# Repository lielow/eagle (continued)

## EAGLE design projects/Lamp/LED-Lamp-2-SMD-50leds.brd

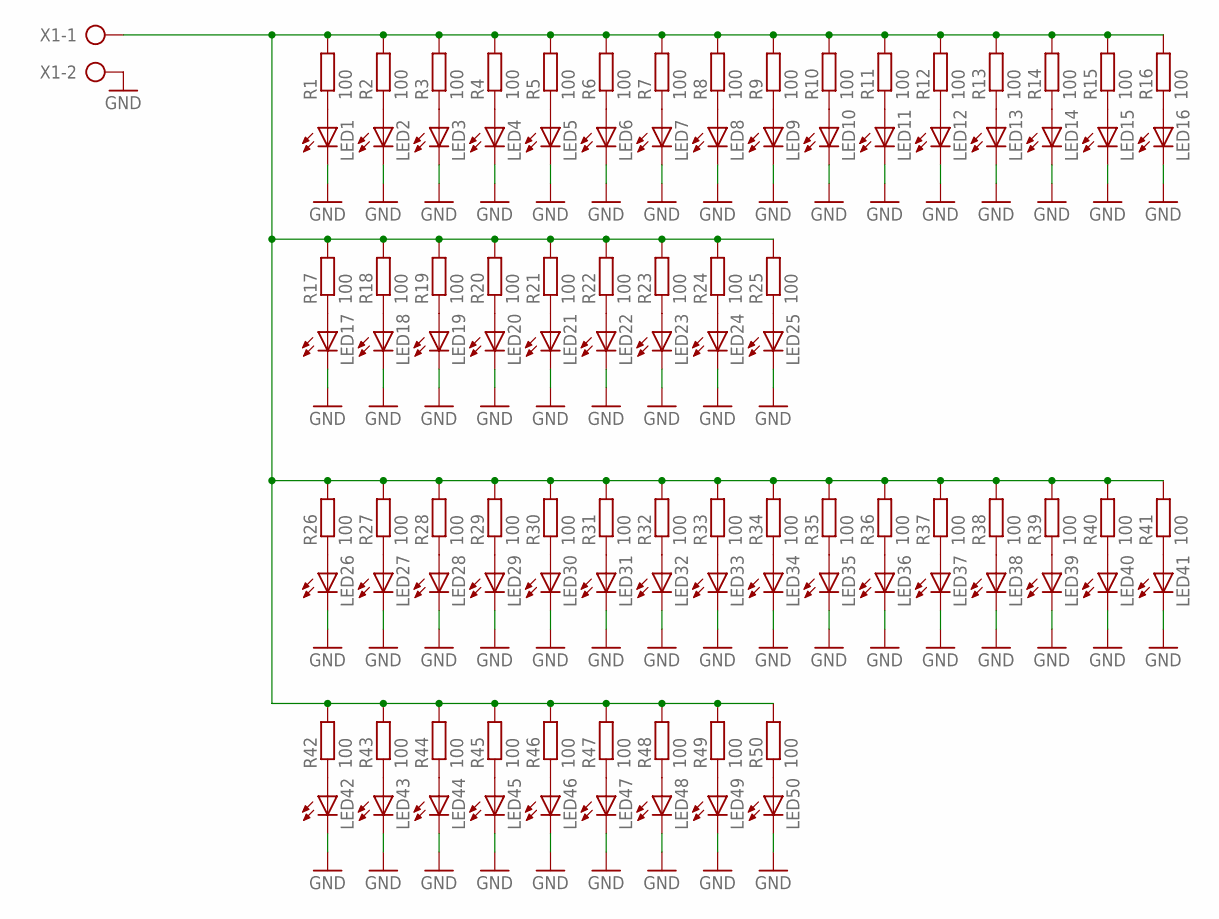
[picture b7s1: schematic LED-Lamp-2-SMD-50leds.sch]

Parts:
LED1, LED2, LED3, LED4, LED5, LED6, LED7, LED8, LED9, LED10, LED11, LED12, LED13, LED14, LED15, LED16, LED17, LED18, LED19, LED20, LED21, LED22, LED23, LED24, LED25, LED26, LED27, LED28, LED29, LED30, LED31, LED32, LED33, LED34, LED35, LED36, LED37, LED38, LED39, LED40, LED41, LED42, LED43, LED44, LED45, LED46, LED47, LED48, LED49, LED50: LEDSML0805; SML0805
R1, R2, R3, R4, R5, R6, R7, R8, R9, R10, R11, R12, R13, R14, R15, R16, R17, R18, R19, R20, R21, R22, R23, R24, R25, R26, R27, R28, R29, R30, R31, R32, R33, R34, R35, R36, R37, R38, R39, R40, R41, R42, R43, R44, R45, R46, R47, R48, R49, R50: 100; M0805
X1: AK300/2

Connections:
GND: LED1.C, LED2.C, LED3.C, LED4.C, LED5.C, LED6.C, LED7.C, LED8.C, LED9.C, LED10.C, LED11.C, LED12.C, LED13.C, LED14.C, LED15.C, LED16.C, LED17.C, LED18.C, LED19.C, LED20.C, LED21.C, LED22.C, LED23.C, LED24.C, LED25.C, LED26.C, LED27.C, LED28.C, LED29.C, LED30.C, LED31.C, LED32.C, LED33.C, LED34.C, LED35.C, LED36.C, LED37.C, LED38.C, LED39.C, LED40.C, LED41.C, LED42.C, LED43.C, LED44.C, LED45.C, LED46.C, LED47.C, LED48.C, LED49.C, LED50.C, X1.2
unnamed: LED1.A, R1.1
unnamed: LED26.A, R26.1
unnamed: LED27.A, R27.1
unnamed: LED2.A, R2.1
unnamed: R1.2, R2.2, R3.2, R4.2, R5.2, R6.2, R7.2, R8.2, R9.2, R10.2, R11.2, R12.2, R13.2, R14.2, R15.2, R16.2, R17.2, R18.2, R19.2, R20.2, R21.2, R22.2, R23.2, R24.2, R25.2, R26.2, R27.2, R28.2, R29.2, R30.2, R31.2, R32.2, R33.2, R34.2, R35.2, R36.2, R37.2, R38.2, R39.2, R40.2, R41.2, R42.2, R43.2, R44.2, R45.2, R46.2, R47.2, R48.2, R49.2, R50.2, X1.1
unnamed: LED3.A, R3.1
unnamed: LED28.A, R28.1
unnamed: LED4.A, R4.1
unnamed: LED29.A, R29.1
unnamed: LED5.A, R5.1
unnamed: LED31.A, R31.1
unnamed: LED6.A, R6.1
unnamed: LED30.A, R30.1
unnamed: LED7.A, R7.1
unnamed: LED32.A, R32.1
unnamed: LED8.A, R8.1
unnamed: LED33.A, R33.1
unnamed: LED9.A, R9.1
unnamed: LED34.A, R34.1
unnamed: LED10.A, R10.1
unnamed: LED35.A, R35.1
unnamed: LED11.A, R11.1
unnamed: LED36.A, R36.1
unnamed: LED12.A, R12.1
unnamed: LED37.A, R37.1
unnamed: LED13.A, R13.1
unnamed: LED38.A, R38.1
unnamed: LED14.A, R14.1
unnamed: LED39.A, R39.1
unnamed: LED15.A, R15.1
unnamed: LED41.A, R41.1
unnamed: LED16.A, R16.1
unnamed: LED40.A, R40.1
unnamed: LED17.A, R17.1
unnamed: LED42.A, R42.1
unnamed: LED18.A, R18.1
unnamed: LED43.A, R43.1
unnamed: LED19.A, R19.1
unnamed: LED44.A, R44.1
unnamed: LED20.A, R20.1
unnamed: LED45.A, R45.1
unnamed: LED21.A, R21.1
unnamed: LED46.A, R46.1
unnamed: LED22.A, R22.1
unnamed: LED47.A, R47.1
unnamed: LED23.A, R23.1
unnamed: LED48.A, R48.1
unnamed: LED24.A, R24.1
unnamed: LED49.A, R49.1
unnamed: LED25.A, R25.1
unnamed: LED50.A, R50.1

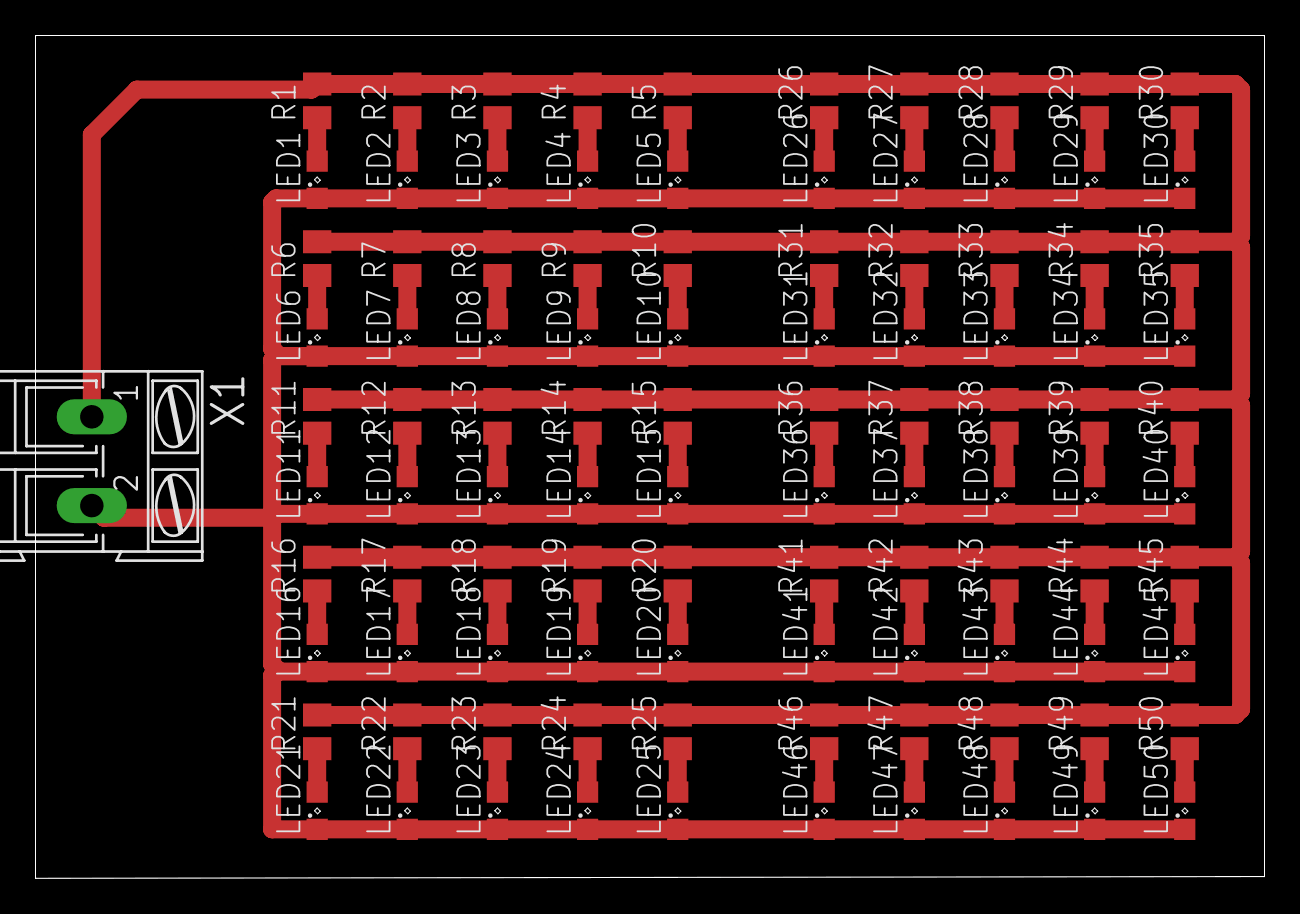
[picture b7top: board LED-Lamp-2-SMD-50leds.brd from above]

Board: 2 copper layers, 69.3 x 47.5 mm, 101 parts (0 on the bottom side), 52 nets.

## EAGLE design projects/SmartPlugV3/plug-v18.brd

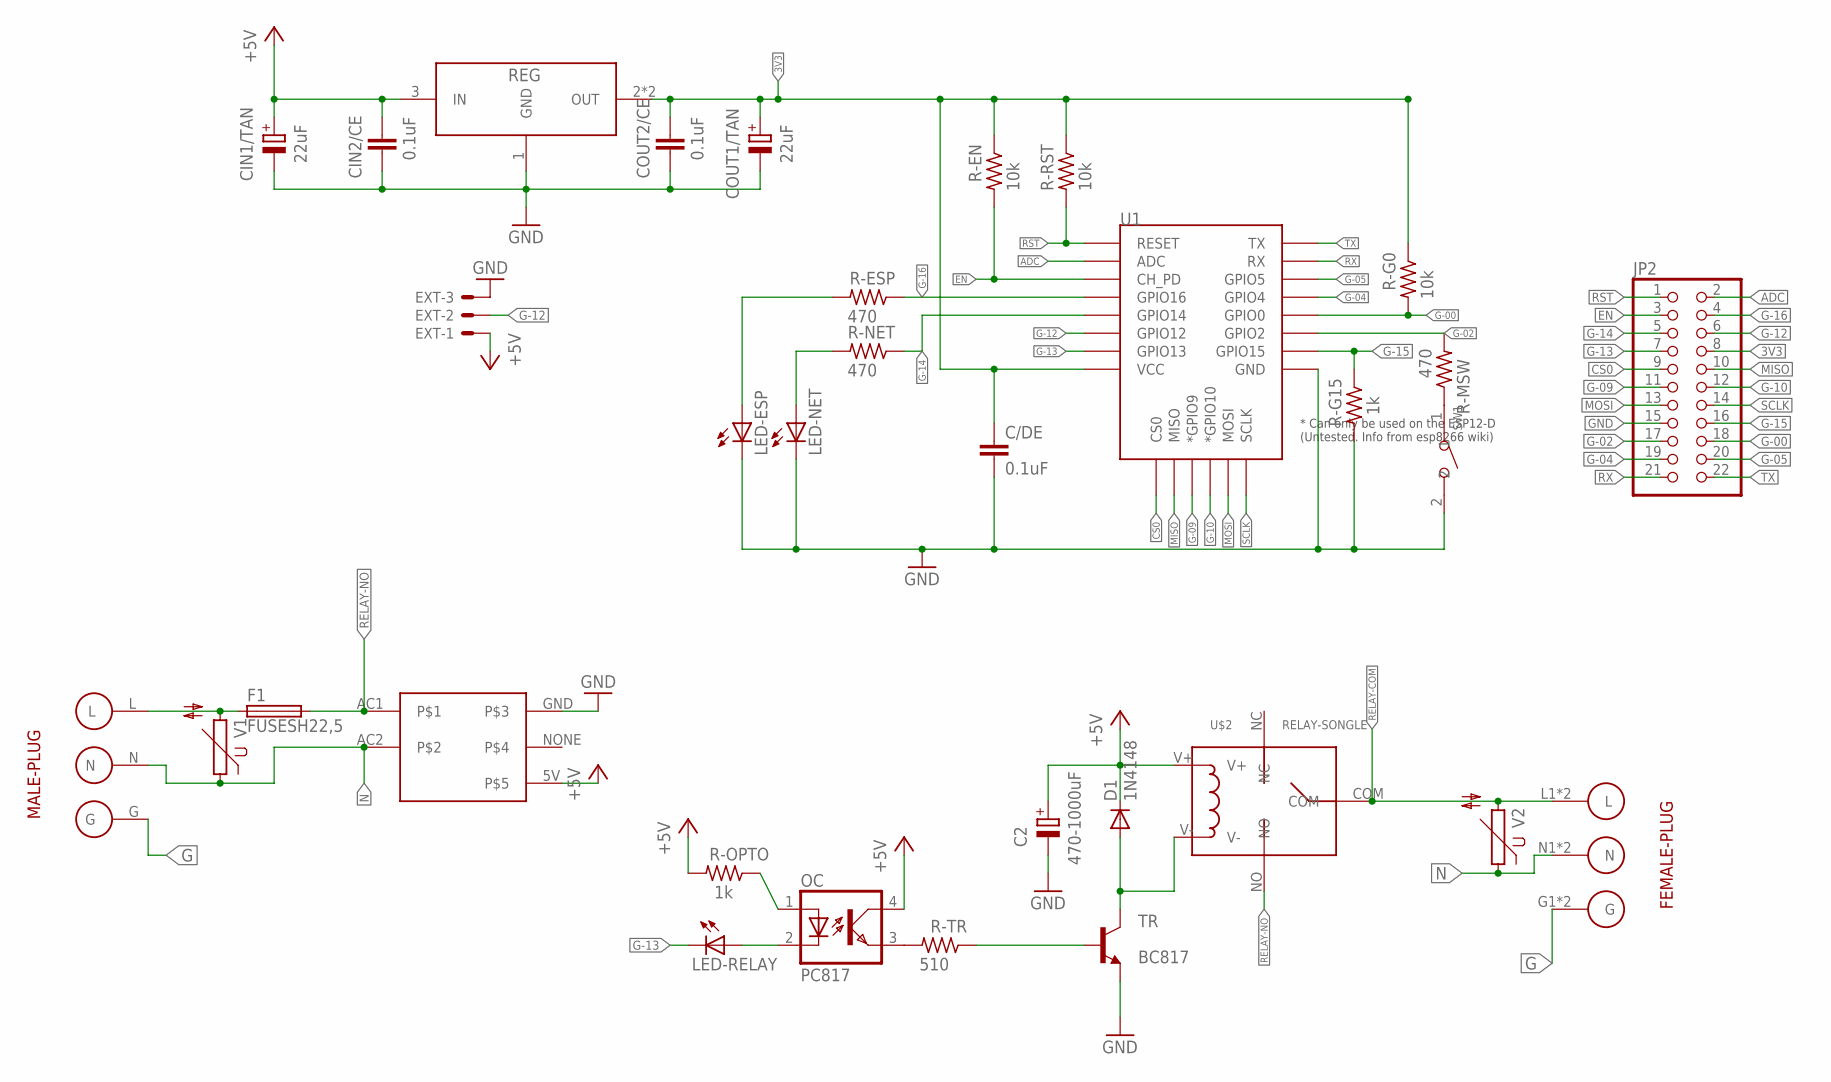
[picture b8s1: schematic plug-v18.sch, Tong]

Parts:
C2: 470-1000uF; E3,5-8
C/DE: 0.1uF; C0805
CIN1/TAN: 22uF; B/3528-21R
CIN2/CE: 0.1uF; C0805K
COUT1/TAN: 22uF; B/3528-21R
COUT2/CE: 0.1uF; C0805K
D1: 1N4148; DO35-7
EXT: 53048-03
F1: FUSESH22,5; SH22,5
JP2: PINHD-2X11; 2X11
LED-ESP: LEDCHIPLED_0805; CHIPLED_0805
LED-NET: LEDCHIPLED_0805; CHIPLED_0805
LED-RELAY: LEDCHIPLED_0805; CHIPLED_0805
OC: PC817; DIL04
R-EN: 10k; M0805
R-ESP: 470; M0805
R-G0: 10k; M0805
R-G15: 1k; M0805
R-MSW: 470; M0805
R-NET: 470; M0805
R-OPTO: 1k; M0805
R-RST: 10k; M0805
R-TR: 510; M0805
REG: AMS1117-3.3; SOT-223
SW1: DIP-BUTTON(2P-6.0X3.0X4.3MM)-TS-1101F; SW2-5.0-6.0X3.0X4.3MM
TR: BC817; SOT23-BEC
U1: ESP12ESMD; ESP12E-SMD
U$2: RELAY-SONGLE
U$3: MALE-PLUG
U$4: POWERSUPPLY-5V-700MA
U$5: FEMALE-PLUG
V1, V2: S14K11

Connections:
3V3: C/DE.1, COUT1/TAN.+, COUT2/CE.1, JP2.8, R-EN.1, R-G0.1, R-RST.1, REG.2 (OUT), REG.4 (OUT), U1.VCC
+5V: C2.+, CIN1/TAN.+, CIN2/CE.1, D1.C, EXT.1, OC.4 (COL), R-OPTO.2, REG.3 (IN), U$2.V+, U$4.5V
ADC: JP2.2, U1.ADC
CS0: JP2.9, U1.CS0
EN: JP2.3, R-EN.2, U1.CH_PD
G: U$3.G, U$5.G1 (G), U$5.G2 (G)
G-00: JP2.18, R-G0.2, U1.GPIO0
G-02: JP2.17, R-MSW.2, U1.GPIO2
G-04: JP2.19, U1.GPIO4
G-05: JP2.20, U1.GPIO5
G-09: JP2.11, U1.GPIO9 (*GPIO9)
G-10: JP2.12, U1.GPIO10 (*GPIO10)
G-12: EXT.2, JP2.6, U1.GPIO12
G-13: JP2.7, LED-RELAY.C, U1.GPIO13
G-14: JP2.5, R-NET.1, U1.GPIO14
G-15: JP2.16, R-G15.1, U1.GPIO15
G-16: JP2.4, R-ESP.1, U1.GPIO16
GND: C2.-, C/DE.2, CIN1/TAN.-, CIN2/CE.2, COUT1/TAN.-, COUT2/CE.2, EXT.3, JP2.15, LED-ESP.C, LED-NET.C, R-G15.2, REG.1 (GND), SW1.2, TR.E, U1.GND, U$4.GND
LINE: F1.1, U$3.L, V1.2
MISO: JP2.10, U1.MISO
MOSI: JP2.13, U1.MOSI
N: U$3.N, U$4.AC2, U$5.N1 (N), U$5.N2 (N), V1.1, V2.1
unnamed: OC.3 (EMIT), R-TR.2
unnamed: R-TR.1, TR.B
unnamed: LED-ESP.A, R-ESP.2
unnamed: OC.1 (A), R-OPTO.1
unnamed: LED-NET.A, R-NET.2
unnamed: D1.A, TR.C, U$2.V-
unnamed: LED-RELAY.A, OC.2 (C)
unnamed: R-MSW.1, SW1.1
RELAY-COM: U$2.COM, U$5.L1 (L), U$5.L2 (L), V2.2
RELAY-NO: F1.2, U$2.NO, U$4.AC1
RST: JP2.1, R-RST.2, U1.RESET
RX: JP2.21, U1.RXD0 (RX)
SCLK: JP2.14, U1.SCLK
TX: JP2.22, U1.TXD0 (TX)

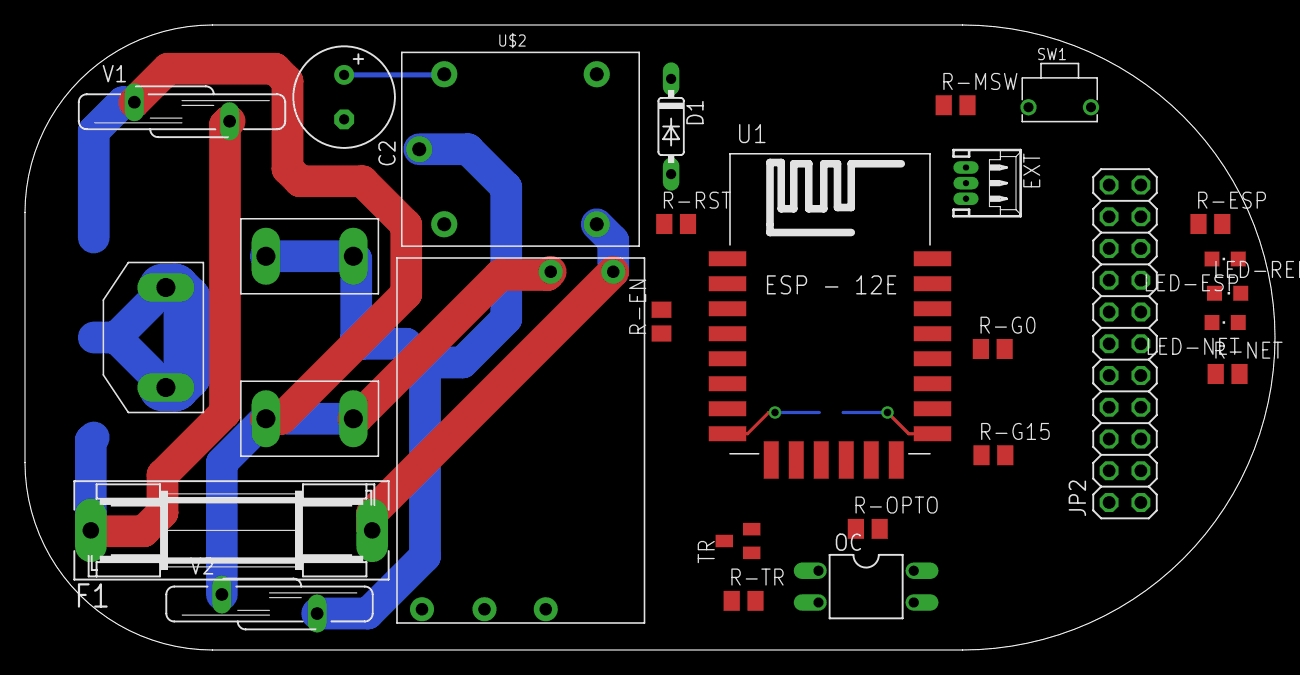
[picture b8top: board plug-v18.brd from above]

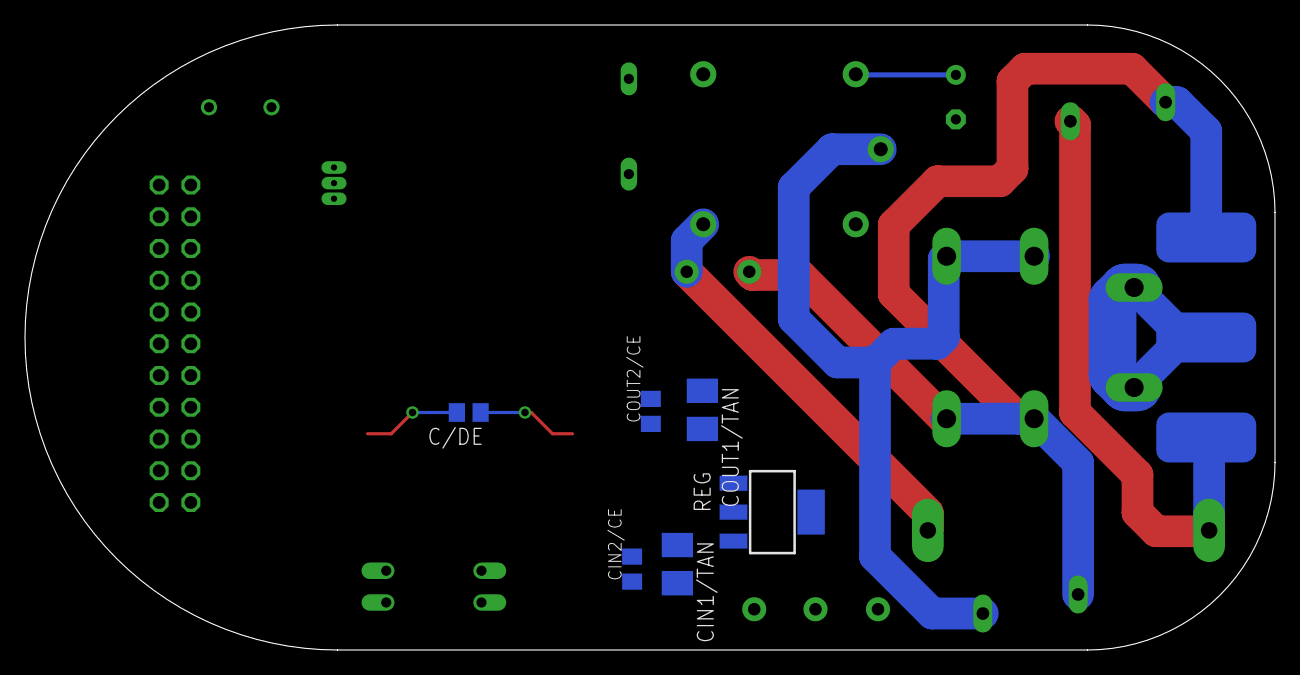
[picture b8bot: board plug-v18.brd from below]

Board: 2 copper layers, 100.0 x 50.0 mm, 33 parts (7 on the bottom side), 36 nets.

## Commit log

2016-06-15 Add README file
2016-06-15 Edit README file
2016-06-15 test
2016-06-15 sdasdada
2016-06-15 sdas
2016-08-14 14-8-59
2016-08-30 commit message
